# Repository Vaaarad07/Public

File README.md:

# PCBs
Repository containing public PCB files

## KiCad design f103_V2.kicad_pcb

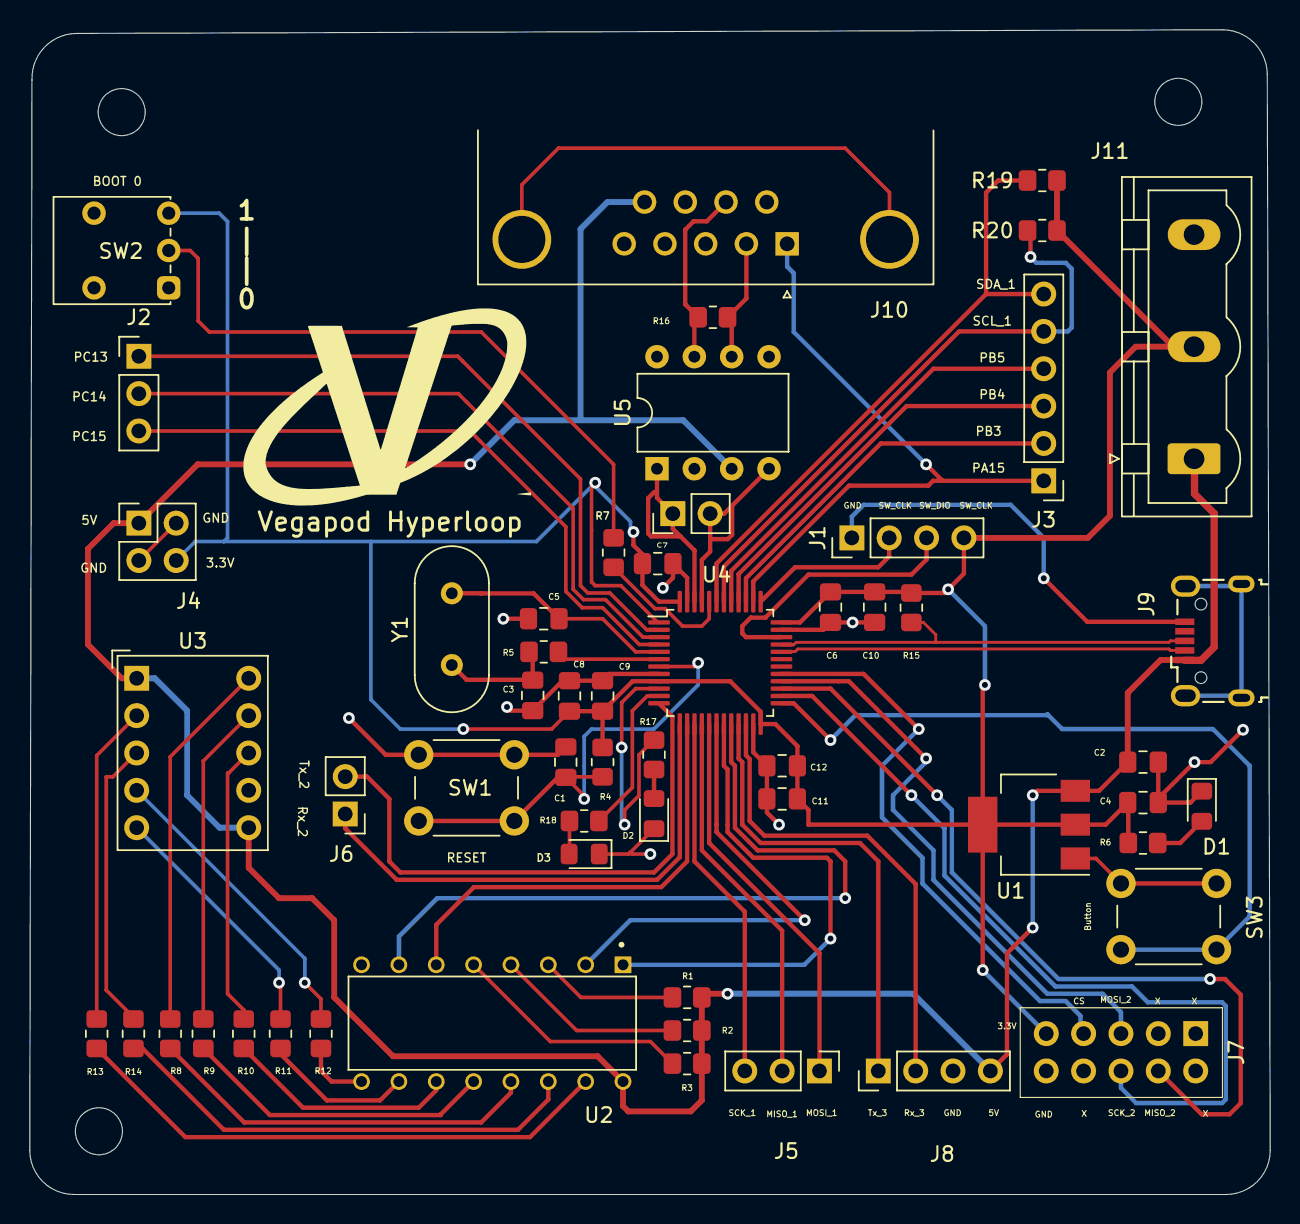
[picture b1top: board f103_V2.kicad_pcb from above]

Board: 2 copper layers, 84.4 x 79.2 mm, 56 parts (1 on the bottom side), 64 nets.

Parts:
C1, C6, C7, C8, C9, C10, C11: 100nF; C_0805_2012Metric_Pad1.18x1.45mm_HandSolder
C2, C4: 22uF; C_0805_2012Metric_Pad1.18x1.45mm_HandSolder
C3, C5: 30pF; C_0805_2012Metric_Pad1.18x1.45mm_HandSolder
C12: 1uF; C_0805_2012Metric_Pad1.18x1.45mm_HandSolder
D1, D2, D3: LED; LED_0805_2012Metric_Pad1.15x1.40mm_HandSolder
J1, J8: Conn_01x04_Male; PinHeader_1x04_P2.54mm_Vertical
J2, J5: Conn_01x03_Male; PinHeader_1x03_P2.54mm_Vertical
J3: Conn_01x06_Male; PinHeader_1x06_P2.54mm_Vertical
J4: Conn_02x02_Odd_Even; PinHeader_2x02_P2.54mm_Vertical
J6, J12: Conn_01x02_Male; PinHeader_1x02_P2.54mm_Vertical
J7: Conn_02x05_Top_Bottom; PinSocket_2x05_P2.54mm_Vertical
J9: USB_B_Micro; USB_Micro-B_Wuerth_629105150521
J10: DB9_Male_MountingHoles; DSUB-9_Male_Horizontal_P2.77x2.84mm_EdgePinOffset4.94mm_Hou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
J11: Conn_01x03_Male; PhoenixContact_GMSTBVA_2,5_3-G-7,62_1x03_P7.62mm_Vertical
R1, R2, R3, R8, R9, R10, R11, R12, R13, R14, R19, R20: R_US; R_0805_2012Metric_Pad1.20x1.40mm_HandSolder
R4, R5, R7: 10k; R_0805_2012Metric_Pad1.20x1.40mm_HandSolder
R6, R15, R17, R18: 1.5k; R_0805_2012Metric_Pad1.20x1.40mm_HandSolder
R16: 120; R_0805_2012Metric_Pad1.20x1.40mm_HandSolder
SW1, SW3: SW_Push; SW_PUSH_6mm_H5mm
SW2: SW_SPDT; SW_Push_1P2T_Vertical_E-Switch_800UDP8P1A1M6
U1: AMS1117-3.3; SOT-223-3_TabPin2
U2: 74LS47; DIP794W45P254L1930H508Q16
U3: SA39-12EWA; Sx39-1xxxxx
U4: STM32F103C8Tx; LQFP-48_7x7mm_P0.5mm
U5: MCP2551-I-SN; DIP-8_W7.62mm
Y1: Crystal; Crystal_HC49-U_Vertical

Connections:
+3.3V: C4.1, C6.1, C7.1, C8.1, C9.1, C10.1, C11.1, C12.1, J1.4, J4.4, J7.9, J11.2, R4.1, R6.2, R15.2, R19.2, R20.2, SW2.3 (C), U1.2 (VO), U4.1 (VBAT), U4.9 (VDDA), U4.24 (VDD), U4.36 (VDD), U4.48 (VDD)
/BOOT0: R7.2, U4.44 (BOOT0)
/CAN_Rx: J12.2, U4.45 (PB8), U5.4 (RXD)
/CAN_Tx: J12.1, U4.46 (PB9), U5.1 (TXD)
/CS: J7.7, U4.29 (PA8)
/Display_A: U2.7 (A), U4.20 (PB2)
/Display_B: U2.1 (B), U4.19 (PB1)
/Display_C: U2.2 (C), U4.18 (PB0)
/Display_D: U2.6 (D), U4.14 (PA4)
/I2C_1_SCL: J3.5, R20.1, U4.42 (PB6)
/I2C_1_SDA: J3.6, R19.1, U4.43 (PB7)
/LED1: R17.2, U4.10 (PA0)
/LED2: R18.2, U4.11 (PA1)
/OSC_IN: C5.2, U4.5 (PD0), Y1.2
/OSC_OUT: R5.1, U4.6 (PD1)
/PA15: J3.1, J10.1, U4.38 (PA15)
/PB4: J3.3, U4.40 (PB4)
/PB5: J3.4, U4.41 (PB5)
/PC13: J2.1, U4.2 (PC13)
/PC14: J2.2, U4.3 (PC14)
/PC15: J2.3, U4.4 (PC15)
/RESET: C1.1, R4.2, SW1.2, U4.7 (NRST)
/SPI_1_MISO: J5.2, U4.16 (PA6)
/SPI_1_MOSI: J5.1, U4.17 (PA7)
/SPI_1_SCK: J5.3, U4.15 (PA5)
/SPI_2_MISO: J7.4, U4.27 (PB14)
/SPI_2_MOSI: J7.5, U4.28 (PB15)
/SPI_2_SCK: J7.6, U4.26 (PB13)
/SW_DIO: J1.3, U4.34 (PA13)
/SW_SCK: J1.2, U4.37 (PA14)
/SW_Trace: J3.2, U4.39 (PB3)
/UART_2_Rx: J6.1, U4.13 (PA3)
/UART_2_Tx: J6.2, U4.12 (PA2)
/UART_3_Rx: J8.2, U4.22 (PB11)
/UART_3_Tx: J8.1, U4.21 (PB10)
/USB_D+: J9.3 (D+), R15.1, U4.33 (PA12)
/USB_D-: J9.2 (D-), U4.32 (PA11)
/Usr_Push_btn: SW3.2, U4.25 (PB12)
GND: C1.2, C2.2, C3.2, C4.2, C5.1, C6.2, C7.2, C8.2, C9.2, C10.2, C11.2, C12.2, D1.1 (K), D2.1 (K), D3.1 (K), J1.1, J4.2, J4.3, J7.10, J8.3, J9.5 (GND), J10.3, J10.6, J11.3, SW1.1, SW2.1 (A), SW3.1, U1.1 (GND), U2.8 (GND), U4.8 (VSSA), U4.23 (VSS), U4.35 (VSS), U4.47 (VSS), U5.2 (VSS), U5.8 (Rs)
unnamed: C3.1, R5.2, Y1.1
unnamed: D1.2 (A), R6.1
unnamed: D2.2 (A), R17.1
unnamed: D3.2 (A), R18.1
unnamed: J10.2, R16.1, U5.6 (CANL)
unnamed: J10.7, R16.2, U5.7 (CANH)
unnamed: R1.2, U2.3 (LT)
unnamed: R2.2, U2.4 (BI)
unnamed: R3.2, U2.5 (RBI)
unnamed: R7.1, SW2.2 (B)
unnamed: R8.1, U2.13 (a)
unnamed: R8.2, U3.10 (A)
unnamed: R9.1, U2.12 (b)
unnamed: R9.2, U3.9 (B)
unnamed: R10.1, U2.11 (c)
unnamed: R10.2, U3.8 (C)
unnamed: R11.1, U2.10 (d)
unnamed: R11.2, U3.5 (D)
unnamed: R12.1, U2.9 (e)
unnamed: R12.2, U3.4 (E)
unnamed: R13.1, U2.15 (f)
unnamed: R13.2, U3.2 (F)
unnamed: R14.1, U2.14 (g)
unnamed: R14.2, U3.3 (G)
VBUS: C2.1, J4.1, J8.4, J9.1 (VBUS), J10.9, J11.1, R1.1, R2.1, R3.1, U1.3 (VI), U2.16 (VCC), U3.1 (CA), U3.6 (CA), U5.3 (VDD)
